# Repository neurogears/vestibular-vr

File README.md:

# vestibular-vr
Closed-loop VR setup for Rancz Lab

[Design Document](https://github.com/neurogears/vestibular-vr/blob/main/Design%20Documents/Vestibular%20VR%20Design%20Document.md)

### Acquisition Prerequisites

The following need to be installed on a fresh system in order to bootstrap the Bonsai environment correctly:

* Windows 10 or greater
* [Visual Studio Code](https://code.visualstudio.com/) (recommended for editing code scripts and git commits)
* [.NET 8.0 SDK](https://dotnet.microsoft.com/en-us/download/dotnet/8.0)
* [.NET Framework 4.7.2 Developer Pack](https://dotnet.microsoft.com/download/dotnet-framework/thank-you/net472-developer-pack-offline-installer) (required for intellisense when editing code scripts)
* [Git for Windows](https://gitforwindows.org/) (recommended for cloning and manipulating this repository)
* [Visual C++ Redistributable for Visual Studio 2012](https://www.microsoft.com/en-us/download/details.aspx?id=30679) (native dependency for OpenCV)
* [FTDI CDM Driver 2.12.28](https://www.ftdichip.com/Drivers/CDM/CDM21228_Setup.zip) (serial port drivers for HARP devices)
* [Spinnaker SDK 1.29.0.5](https://www.teledynevisionsolutions.com/support/support-center/software-firmware-downloads/iis/spinnaker-sdk-download/spinnaker-sdk--download-files) (device drivers for FLIR cameras, sign in required, look in the archived stable versions for 1.29.0.5)

### Setting up the Bonsai environment

To set up a Bonsai environment for running vestibular-vr, use the terminal to clone the repo into a local folder:

``` 
git clone https://github.com/neurogears/vestibular-vr.git
```

Now navigate into vestibular-vr/bonsai folder and run the `Setup.ps1` script (on Windows right-click > Run with powershell). Once all dependencies have been restored Bonsai can be launched in a local environment from the `.exe` in this folder.

### Session settings

Experiment parameters are based on a json schema (`schema.json` in the repo). Implementations of this schema are defined in `.yml` files provided by the user that are then loaded in the main Bonsai workflow to set up experiment parameters.

#### Working with schemas in Visual Studio Code
To create and edit schema implementations with full autcomplete and hinting, Visual Studio Code requires some extensions to be added:
* json (ZainChen.json)
* JSON Schema Validator (tberman.json-schema-validator)
* YAML (redhat.vscode-yaml)

#### Creating an experiment parameter file
To create an experiment parameter file based on the `schema`, create a new `.yml` file and add a reference to the `schema` at the top of the file

```
%YAML 1.1
---
# yaml-language-server: $schema=schema.json
```

The `schema` has two main groups of properties that define global experiment parameters, and block-specific parameters respectively, e.g.:

```
metadata:
  animalId: plimbo
  rootPath: D:/TrialLogicTestData/
  runGain: 0.0005

blocks: [
  &blockA
  {
    stimulus: {type: "grating"},
    totalRuntime: 20,
    runThreshold: 100,
    decayTimestep: 0.1,
    runThresholdDecay: -1,
    haltProbability: 0.5,
    haltProtocol: {
      minumumDelay: 0.1,
      randomDelay: 1.5,
      haltTime: 2,
      haltGain: 0
    }
  },
  &blockB
  {
    stimulus: {type: "cloud"},
    totalRuntime: 140,
    runThreshold: 200,
    decayTimestep: 0.1,
    runThresholdDecay: -1,
    haltProbability: 0.7,
    haltProtocol: {
      minumumDelay: 0.1,
      randomDelay: 0.5,
      haltTime: 0.5,
      haltGain: 0
    }
  },
  {<<: *blockA},
  {<<: *blockB}
]
```

The description of each parameter's effect on the Bonsai workflow, along with its type and default values are defined within `schema.json` itself. Note that where a parameter is not specifically set in the `.yml` the value will revert the default.

### Running an experiment
To run an experiment, run the Bonsai application from the local environment and open Main.bonsai. Use the property grid to select the desired experiment parameter `.yml` file.

### Gain settings
The `schema` has a number of gain settings that can be used to flexibly the define the relationship between real-time data sources (ball movement, encoder reading, file playback) and closed-loop outputs like visual field movement or motor movement. These gains are applied hierarchically with some affecting all calculations, and some defined per-block or per-source:

- `runGain` - global gain applied to all calculations
  - `blockGainModifier` - additional gain specific to a block
    - Visual: gains that contribute to visual field motion
      - `flowXToVisualGain` - gain applied to optical sensor X reading
      - `flowYToVisualGain` - gain applied to optical sensor Y reading
      - `rotaryToVisualGain` - gain applied to the rotary encoder reading
      - `playbackToVisualGain` - gain applied to the file playback data source
    - Motor: gains that contribute to motor motion
      - `flowXToMotorGain` - gain applied to optical sensor X reading
      - `flowYToMotorGain` - gain applied to optical sensor Y reading
      - `playbackToMotorGain` - gain applied to the file playback data source
  - `haltGain` - set as part of a `haltProtocol`. Applies a gain to all sources during a halt, block-specific.

We use the term 'procession' to describe the movement delta of the visual field or motor in response to an update from a data source (optical flow, playback etc.) on a given trial. Let `h` be a variable that describes whether a halt is currently happening (1 = halt happening, 0 = halt not happening), visual and motor processions are defined as:

```
visualProcession = (runGain * blockGainModifier) * (flowXToVisualGain*flowX + flowYToVisualGain*flowY + rotaryToVisualGain*encoder + playbackToVisualGain*playback) * (haltGain*h)
```
```
motorProcession = (runGain * blockGainModifier) * (flowXToMotorGain*flowX + flowYToMotorGain*flowY + playbackToVisualGain*playback) * (haltGain*h)
```

`motorProcession` is converted by the function `ToPulseInterval` to an immediate pulse interval command which is written to the motor. The conversion between this command and the speed of the motor is dependent on the hardware settings for pulse interval --> motor motion on the motor controller.
The relationship of `visualProcession` to visual field movement is dependent on the current visual stimulus being presented. For example for a gratings stimulus, the value represents the absolute phase angle of the gratings being shown. For a motion clouds stimulus, it represents the (wrapped) index of the motion cloud frame being shown.

Gains can be set to modify the contribution of a data source to procession, for example to specify a block where visual motion is only dependent on the X value of the flow sensor we can set:

```
# metadata
runGain: 0.0008 # represents final conversion from procession to visual angle
# block settings
blockGainModifier: 1 # block modifier does not scale input data sources
flowXToVisualGain: 1 # we want the X flow value to contribute
flowYToVisualGain: 0 # we don't want the Y flow value to contribute
rotaryToVisualGain: 0 # encoder reading should not contribute
playbackToVisualGain: 0 # playback source should not contribute
```

### Optical flow sensor smoothing

An average smoothing function is applied to the optical sensor reading. A `schema` parameter `flowSmoothing` is applied per-block which specifies a count of how many samples to smooth over, i.e. the length of the buffer to take an average, smoothed value from.

### Data logging
Data is logged according to the [Aeon.Acquisition](https://github.com/SainsburyWellcomeCentre/aeon_acquisition) format. Generally, data is grouped according to a folder named with a timestamp representing the start time of an experiment. Within this folder, data is organised by **device**, where a device may be a camera, Harp board, ONIX acquisition etc. For longer experiments, data is 'chunked' by hour such that the full raw data is split across multiple files to ensure no single file grows unmanageably large.

Within each device, data may be stored in a different format according to the device's data output. In general however, there will be a log of the raw data (e.g. camera frames, sensor readings) and a corresponding source of timestamps to allow for relating the data to the Harp clock. For a camera, this will take the form of a video file with the acquired camera frames, as well as a corresponding .csv file with paired Harp timestamps and camera frame indices. For a Harp device, this will take the form of a flat binary file organised by individual register, with the output of that register paired with a Harp timestamp.

As Harp files are saved as flat binary, it is recommended to use the device schema for that Harp device to parse the individual values and read the correct data type.

### Python environment

The following need to be installed once on a new system in order to analyze data:

 * [Visual Studio Code](https://code.visualstudio.com/) (recommended for editing code scripts and git commits)
 * A Conda distribution such as [Miniconda](https://docs.anaconda.com/free/miniconda/index.html)
 * [Python Extension for VS Code](https://marketplace.visualstudio.com/items?itemName=ms-python.python)
   * This extension needs to be made aware of the Conda installation. To do so, navigate to the extension settings. Under the section **Python: Conda Path**, enter the full path to the conda.bat executable. ([more info](https://stackoverflow.com/a/77615160/3312269).)
 * [Jupyter Extension for VS Code](https://marketplace.visualstudio.com/items?itemName=ms-toolsai.jupyter)

#### Create local Environment
1. Open the vestibular-vr folder in VS Code
2. `Ctrl+Shift+P` in VS Code > Python: Create Environment
   * Select Conda
   * Select Python 3.11 kernel
3. Ensure pip is upgraded:
 ```
 pip install --upgrade pip
 ```
4. From the terminal run `pip install -r requirements.txt`
5. Clone aeon_mecha into a separate directory 
 ```
 git clone https://github.com/SainsburyWellcomeCentre/aeon_mecha.git 
 ```
6. From the VS Code terminal, `cd` into the aeon_mecha directory and run:
 ```
 python -m pip install -e .
 ```

 ### SLEAP
 Follow the standard instructions for [installing SLEAP](https://sleap.ai/installation.html), [creating a project](https://sleap.ai/tutorials/new-project.html) and [labeling](https://sleap.ai/tutorials/initial-labeling.html). Ensure that you use training videos of the same pixel width and height that you will use for inference later. During training, ensure you select `single animal` as the training pipeline type, and that the image is converted to grayscale.

 After completing training, activate the sleap conda environment (if not already activated) and run:

 ```
sleap-export -m /model/folder/path
 ```

 to export the trained model to a format that can be used by Bonsai.

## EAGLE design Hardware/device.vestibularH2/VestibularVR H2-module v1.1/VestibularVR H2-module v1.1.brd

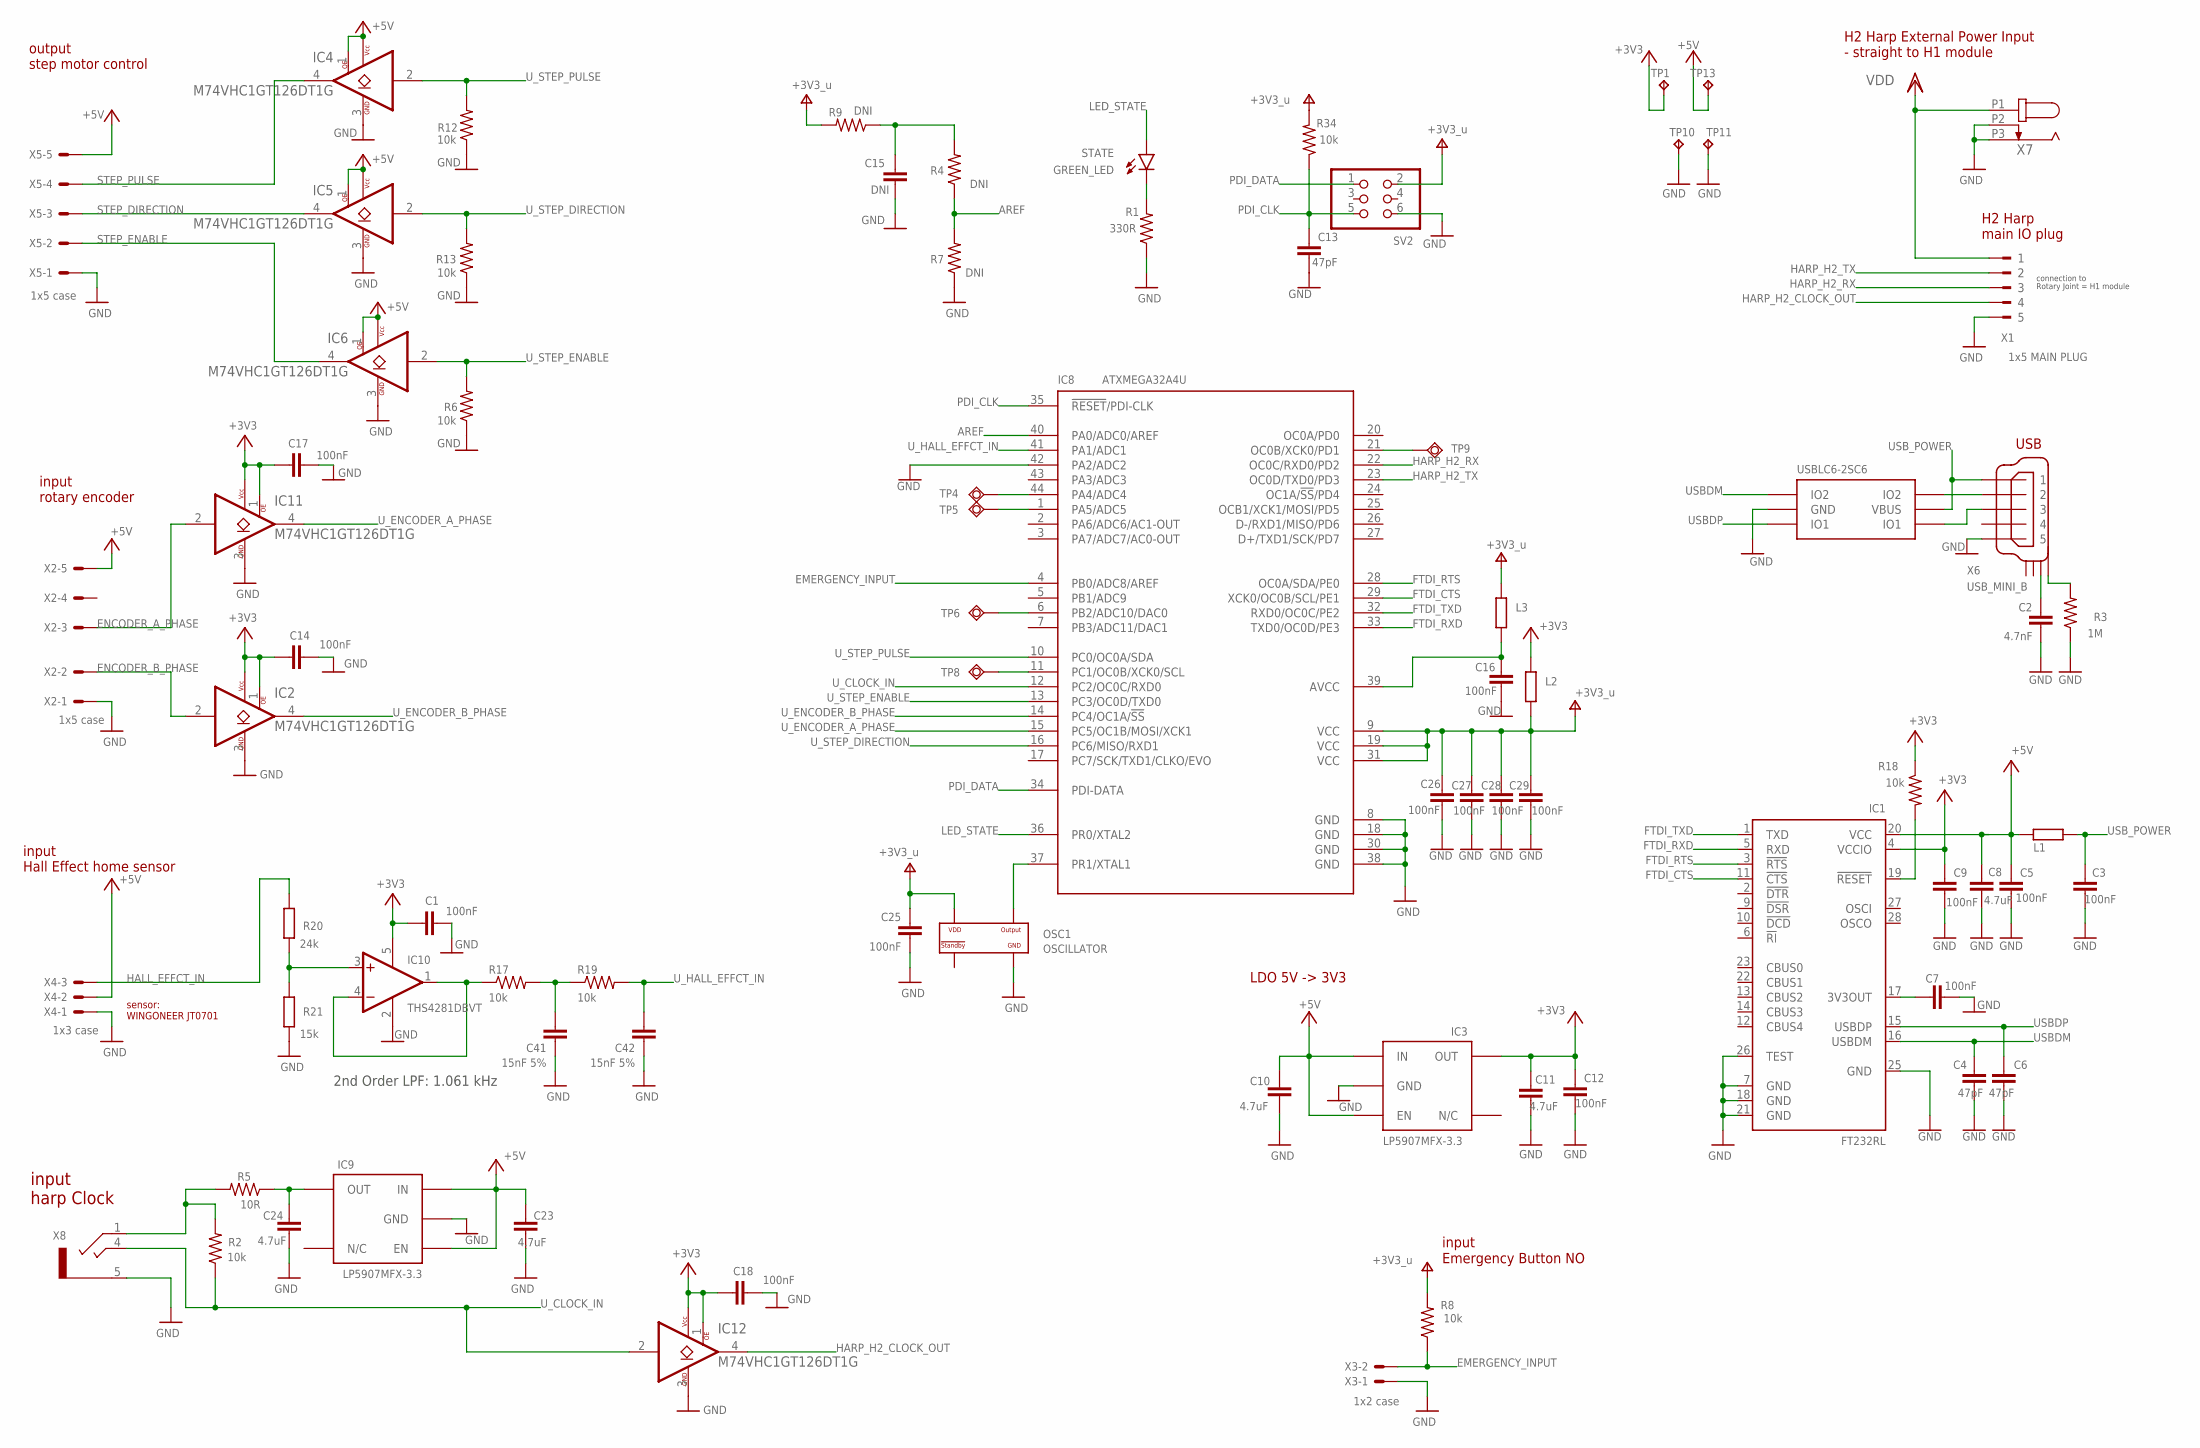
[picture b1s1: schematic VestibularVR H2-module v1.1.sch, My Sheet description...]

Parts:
C1, C3, C5, C7, C9, C12, C14, C16, C17, C18, C25, C26, C27, C28, C29: 100nF; C0402K; MPN C1005X7R1H104K050BB
C2: 4.7nF; C0402K; MPN CC0402KRX7R8BB472
C4, C6, C13: 47pF; C0402K; MPN 04025A470JAT2A
C8, C10, C11, C23, C24: 4.7uF; C0603K; MPN C1608X6S1C475K080AC
C15: DNI; C0603K; MPN DNI
C41, C42: 15nF 5%; C0402K; MPN CGA2B3X7R1V153K050BB
IC1: FT232RL; SSOP28; MPN FT232RL
IC2, IC4, IC5, IC6, IC11, IC12: M74VHC1GT126DT1G; TSOP-5; MPN M74VHC1GT126DT1G; DIGIKEY_PN M74VHC1GT126DT1GOSDKR-ND
IC3, IC9: LP5907MFX-3.3; TSOT23-5; MPN LP5907MFX-3.3/NOPB
IC7: USBLC6-2SC6; SOT23-6L; MPN USBLC6-2SC6
IC8: ATXMEGA32A4U; TQFP44; MPN ATXMEGA32A4U-AUR
IC10: THS4281DBVT; SOT23-5; MPN THS4281DBVT
L1, L2, L3: 40R@100MHz; R0805; MPN MI0805K400R-10
OSC1: OSCILLATOR; OSCILLATOR_3.2X2.5; MPN DSC1001CI5-032.0000
R1: 330R; R0402; MPN RC0402FR-07330RL
R2, R6, R8, R12, R13, R17, R18, R19, R34: 10k; R0402; MPN CRCW040210K0FKED
R3: 1M; R0402; MPN CRCW04021M00FKED
R4, R7, R9: DNI; R0402; MPN DNI
R5: 10R; R0402; MPN ERJ-PA2J100X
R20: 24k; R0402; MPN ERJ-2RKF2402X
R21: 15k; R0402; MPN ERJ-2RKF1502X
STATE: GREEN_LED; CHIP-LED0603; MPN LTST-C191KGKT
SV2: PINHD-2X3; 2X03; MPN 609-3210-ND
TP1, TP10, TP11, TP13: NO_COMPONENT; B1,27
TP4, TP5, TP6, TP8, TP9: NO_COMPONENT; TP11R
X1: 1x5 MAIN PLUG; 90G-5; MPN 20.155MH/5-E
X2, X5: 1x5 case; 22-23-2051; MPN 282834-5
X3: 1x2 case; 22-23-2021; MPN 282834-2
X4: 1x3 case; 22-23-2031; MPN 282834-3
X6: USB_MINI_B; 240-0002-1; MPN UX60-MB-5S8
X7: DC_JACK2.1MM; DC_POWER_INPUT_2.1MM; MPN 163-179PH-EX
X8: CLCK_JACK; 35RASMT2BHNTRX; MPN 35RASMT2BHNTRX

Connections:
+3V3: C1.1, C9.1, C11.1, C12.1, C14.1, C17.1, C18.1, IC1.4 (VCCIO), IC2.1 (OE), IC2.5 (VCC), IC3.5 (OUT), IC10.5 (V+), IC11.1 (OE), IC11.5 (VCC), IC12.1 (OE), IC12.5 (VCC), L2.2, R18.1, TP1.TP
+5V: C5.1, C8.1, C10.1, C23.1, IC1.20 (VCC), IC3.1 (IN), IC3.3 (EN), IC4.1 (OE), IC4.5 (VCC), IC5.1 (OE), IC5.5 (VCC), IC6.1 (OE), IC6.5 (VCC), IC9.1 (IN), IC9.3 (EN), L1.1, TP13.TP, X2.5, X4.2, X5.5
AREF: IC8.40 (PA0/ADC0/AREF), R4.1, R7.2
EMERGENCY_INPUT: IC8.4 (PB0/ADC8/AREF), R8.1, X3.2
ENCODER_A_PHASE: IC11.2 (A), X2.3
ENCODER_B_PHASE: IC2.2 (A), X2.2
FTDI_CTS: IC1.11 (!CTS), IC8.29 (XCK0/OC0B/SCL/PE1)
FTDI_RTS: IC1.3 (!RTS), IC8.28 (OC0A/SDA/PE0)
FTDI_RXD: IC1.5 (RXD), IC8.33 (TXD0/OC0D/PE3)
FTDI_TXD: IC1.1 (TXD), IC8.32 (RXD0/OC0C/PE2)
GND: C1.2, C2.2, C3.2, C4.2, C5.2, C6.2, C7.2, C8.2, C9.2, C10.2, C11.2, C12.2, C13.2, C14.2, C15.2, C16.2, C17.2, C18.2, C23.2, C24.2, C25.2, C26.2, C27.2, C28.2, C29.2, C41.1, C42.1, IC1.7 (GND), IC1.18 (GND), IC1.21 (GND), IC1.25 (GND), IC1.26 (TEST), IC2.3 (GND), IC3.2 (GND), IC4.3 (GND), IC5.3 (GND), IC6.3 (GND), IC7.P$2 (GND), IC8.8 (GND), IC8.18 (GND), IC8.30 (GND), IC8.38 (GND), IC8.42 (PA2/ADC2), IC9.2 (GND), IC10.2 (V-), IC11.3 (GND), IC12.3 (GND), OSC1.P$2 (GND), R1.1, R3.1, R6.1, R7.1, R12.1, R13.1, R21.1, SV2.6, TP10.TP, TP11.TP, X1.5, X2.1, X3.1, X4.1, X5.1, X6.P$5 (5), X7.P2 (2), X7.P3 (3), X8.5
HALL_EFFCT_IN: R20.2, X4.3
HARP_H2_CLOCK_OUT: IC12.4 (Y), X1.4
HARP_H2_RX: IC8.22 (OC0C/RXD0/PD2), X1.3
HARP_H2_TX: IC8.23 (OC0D/TXD0/PD3), X1.2
LED_STATE: IC8.36 (PR0/XTAL2), STATE.A
unnamed: R3.2, X6.SHIELD_4
unnamed: IC7.P$4 (IO2), X6.P$2 (2)
unnamed: IC7.P$6 (IO1), X6.P$3 (3)
unnamed: R1.2, STATE.C
unnamed: IC8.44 (PA4/ADC4), TP4.TP
unnamed: IC8.1 (PA5/ADC5), TP5.TP
unnamed: IC8.6 (PB2/ADC10/DAC0), TP6.TP
unnamed: C2.1, X6.SHIELD_3
unnamed: IC8.11 (PC1/OC0B/XCK0/SCL), TP8.TP
unnamed: IC8.21 (OC0B/XCK0/PD1), TP9.TP
unnamed: C7.1, IC1.17 (3V3OUT)
unnamed: C41.2, R17.2, R19.1
unnamed: C15.1, R4.2, R9.1
unnamed: C16.1, IC8.39 (AVCC), L3.1
unnamed: IC10.1 (OUT), IC10.4 (-IN), R17.1
unnamed: IC10.3 (+IN), R20.1, R21.2
unnamed: R2.2, R5.2, X8.1
unnamed: C24.1, IC9.5 (OUT), R5.1
unnamed: IC1.19 (!RESET), R18.2
OSC2: IC8.37 (PR1/XTAL1), OSC1.P$3 (OUTPUT)
PDI_CLK: C13.1, IC8.35 (!RESET!/PDI-CLK), R34.1, SV2.5
PDI_DATA: IC8.34 (PDI-DATA), SV2.1
STEP_DIRECTION: IC5.4 (Y), X5.3
STEP_ENABLE: IC6.4 (Y), X5.2
STEP_PULSE: IC4.4 (Y), X5.4
USBDM: C4.1, IC1.16 (USBDM), IC7.P$3 (IO2)
USBDP: C6.1, IC1.15 (USBDP), IC7.P$1 (IO1)
USB_POWER: C3.1, IC7.P$5 (VBUS), L1.2, X6.P$1 (1)
U_CLOCK_IN: IC8.12 (PC2/OC0C/RXD0), IC12.2 (A), R2.1, X8.4
U_ENCODER_A_PHASE: IC8.15 (PC5/OC1B/MOSI/XCK1), IC11.4 (Y)
U_ENCODER_B_PHASE: IC2.4 (Y), IC8.14 (PC4/OC1A/!SS)
U_HALL_EFFCT_IN: C42.2, IC8.41 (PA1/ADC1), R19.2
U_STEP_DIRECTION: IC5.2 (A), IC8.16 (PC6/MISO/RXD1), R13.2
U_STEP_ENABLE: IC6.2 (A), IC8.13 (PC3/OC0D/TXD0), R6.2
U_STEP_PULSE: IC4.2 (A), IC8.10 (PC0/OC0A/SDA), R12.2
V+: C25.1, C26.1, C27.1, C28.1, C29.1, IC8.9 (VCC), IC8.19 (VCC), IC8.31 (VCC), L2.1, L3.2, OSC1.P$4 (VDD), R8.2, R9.2, R34.2, SV2.2
VDD: X1.1, X7.P1 (1)

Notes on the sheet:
H2 Harp main IO plug
input rotary encoder
input Hall Effect home sensor
input harp Clock
output step motor control
input Emergency Button NO
USB
sensor: WINGONEER JT0701
H2 Harp External Power Input - straight to H1 module
connection to Rotary Joint = H1 module
2nd Order LPF: 1.061 kHz
LDO 5V -> 3V3

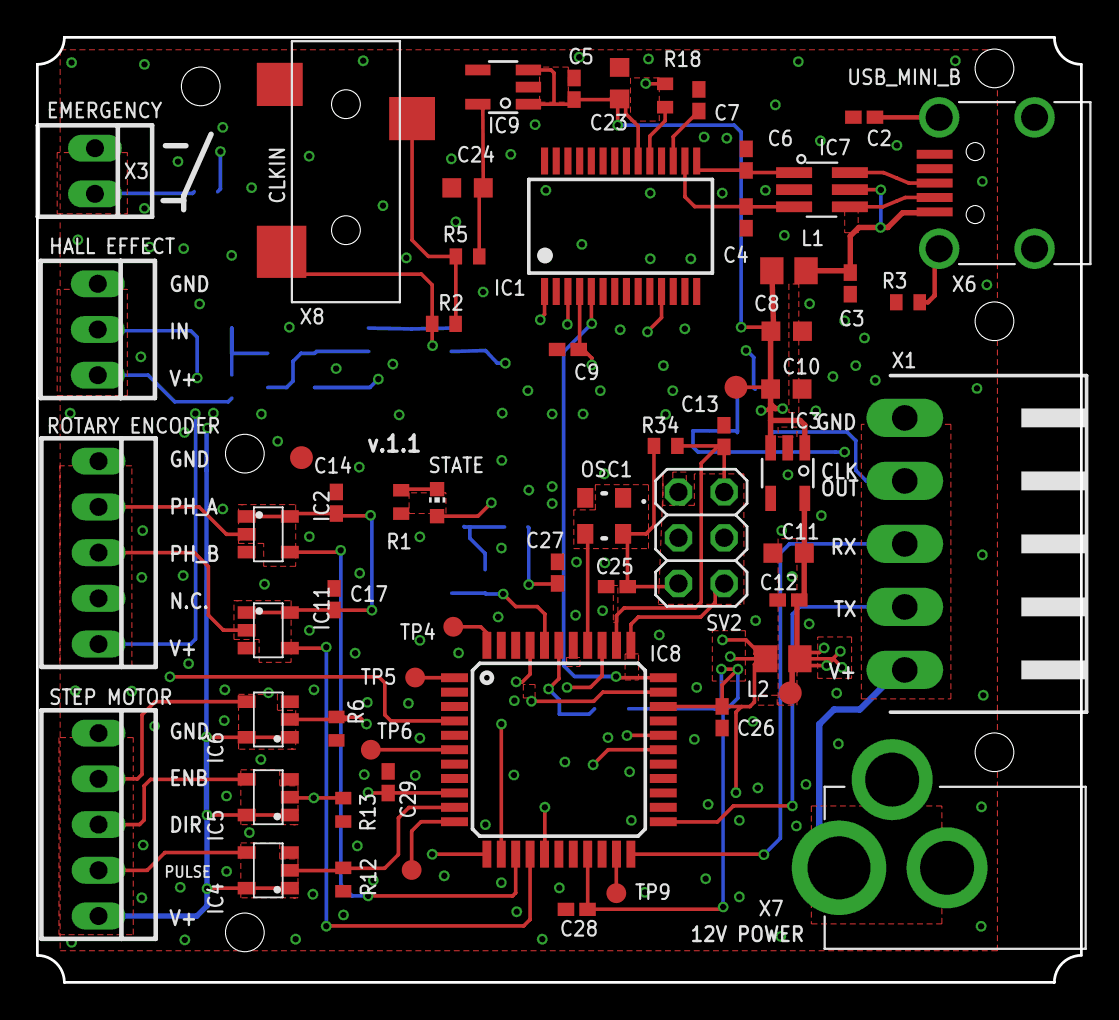
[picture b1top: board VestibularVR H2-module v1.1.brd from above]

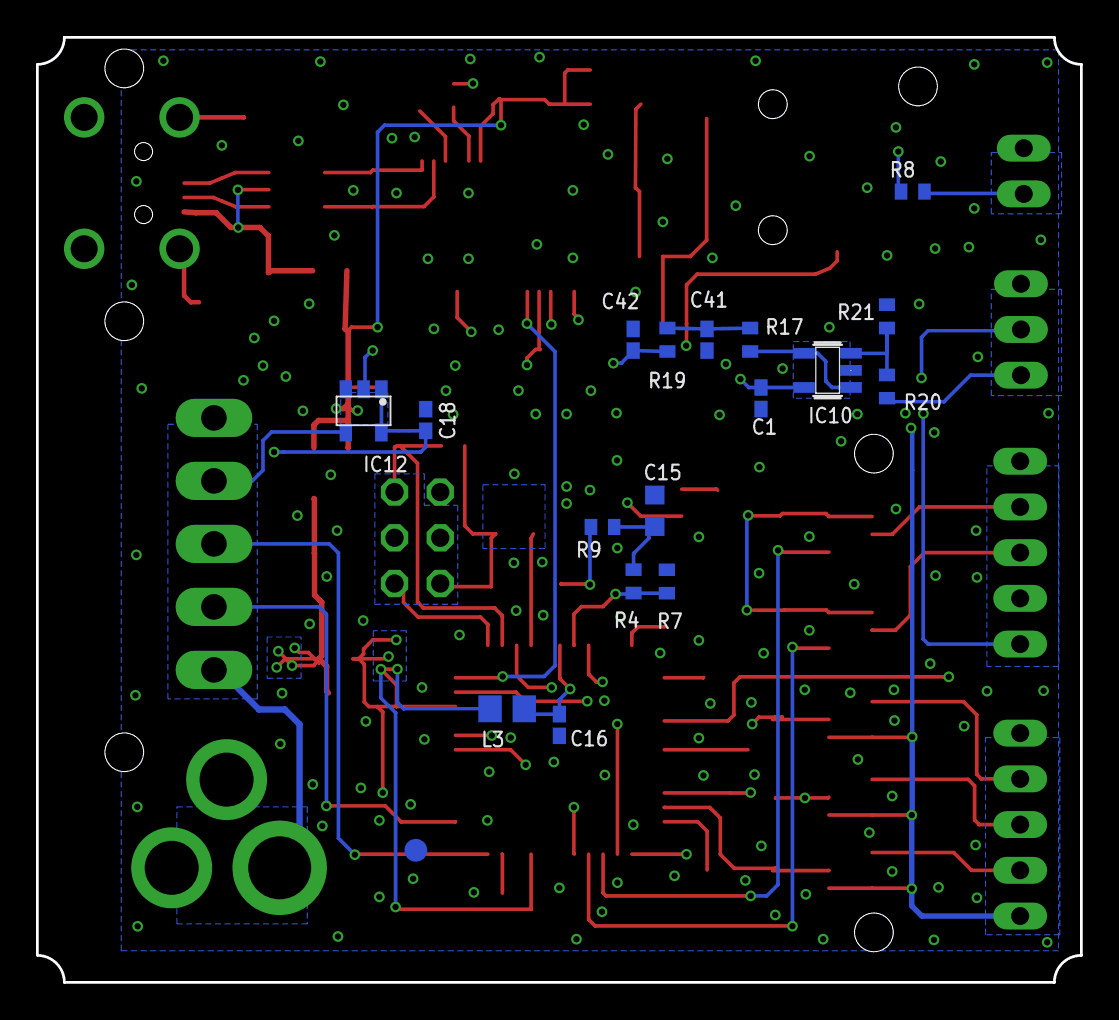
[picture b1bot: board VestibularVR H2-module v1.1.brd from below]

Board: 4 copper layers, 58.0 x 52.5 mm, 79 parts (18 on the bottom side), 53 nets.

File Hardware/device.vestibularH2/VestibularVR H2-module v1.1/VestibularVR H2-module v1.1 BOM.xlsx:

VestibularVR H2-module v1.1
.on board
Qty | Parts | Value | OEPS | MPN | Device | Package | Description
15 | C1, C3, C5, C7, C9, C12, C14, C16, C17, C18, C25, C26, C27, C28, C29 | 100nF | OEPS010004 | C1005X7R1H104K050BB | C-EUC0402K | C0402K | CAPACITOR, European symbol
1 | R5 | 10R | OEPS020041 | ERJ-PA2J100X | R-US_R0402 | R0402 | RESISTOR, American symbol
9 | R2, R6, R8, R12, R13, R17, R18, R19, R34 | 10k | OEPS020030 | CRCW040210K0FKED | R-US_R0402 | R0402 | RESISTOR, American symbol
1 | R21 | 15k | OEPS020015 | ERJ-2RKF1502X | R-EU_R0402 | R0402 | RESISTOR, European symbol
2 | C41, C42 | 15nF 5% | OEPS010023 | CGA2B3X7R1V153K050BB | C-EUC0402K | C0402K | CAPACITOR, European symbol
1 | R3 | 1M | OEPS020026 | CRCW04021M00FKED | R-US_R0402 | R0402 | RESISTOR, American symbol
1 | X3 | 1x2 case | OEPS070020 | 282834-2 | 22-23-2021 | 22-23-2021 | .100 (2.54mm) Center Header - 2 Pin"
1 | X4 | 1x3 case | OEPS070035 | 282834-3 | 22-23-2031 | 22-23-2031 | .100 (2.54mm) Center Header - 3 Pin"
1 | X1 | 1x5 MAIN PLUG | OEPS070037 | 20.155MH/5-E | 90G-5 | 90G-5 | WEIDMUELLER CLAMP CONNECTOR
2 | X2, X5 | 1x5 case | OEPS070041 | 282834-5 | 22-23-2051 | 22-23-2051 | .100 (2.54mm) Center Header - 5 Pin"
1 | R20 | 24k | OEPS020048 | ERJ-2RKF2402X | R-EU_R0402 | R0402 | RESISTOR, European symbol
1 | R1 | 330R | OEPS020037 | RC0402FR-07330RL | R-US_R0402 | R0402 | RESISTOR, American symbol
1 | C2 | 4.7nF | OEPS010001 | CC0402KRX7R8BB472 | C-EUC0402K | C0402K | CAPACITOR, European symbol
5 | C8, C10, C11, C23, C24 | 4.7uF | OEPS010018 | C1608X6S1C475K080AC | C-EUC0603K | C0603K | CAPACITOR, European symbol
3 | L1, L2, L3 | 40R@100MHz | OEPS040003 | MI0805K400R-10 | R-EU_R0805 | R0805 | RESISTOR, European symbol
3 | C4, C6, C13 | 47pF | OEPS010011 | 04025A470JAT2A | C-EUC0402K | C0402K | CAPACITOR, European symbol
1 | IC8 | ATXMEGA32A4U | OEPS080012 | ATXMEGA32A4U-AUR | XMEGA-A4_AT-XMEGA-XXA4-AUTQFP44 | TQFP44 | ATxMega a4 Serie
1 | X8 | CLCK_JACK | OEPS070025 | 35RASMT2BHNTRX | STEREO_JACK | 35RASMT2BHNTRX | CONN JACK STEREO 3.5MM SMD R/A
1 | X7 | DC_JACK2.1MM | OEPS070026 | 163-179PH-EX | DC_JACK2.1MM | DC_POWER_INPUT_2.1MM | DC Power Connectors PCB 2.1MM
1 | C15 | DNI | DNI | DNI | C-EUC0603K | C0603K | CAPACITOR, European symbol
3 | R4, R7, R9 | DNI | DNI | DNI | R-US_R0402 | R0402 | RESISTOR, American symbol
1 | IC1 | FT232RL | OEPS080013 | FT232RL | FT232RL | SSOP28 | UART/FIFO IC
1 | STATE | GREEN_LED | OEPS030005 | LTST-C191KGKT | LEDCHIP-LED0603 | CHIP-LED0603
2 | IC3, IC9 | LP5907MFX-3.3 | OEPS080016 | LP5907MFX-3.3/NOPB | TLV700XX | TSOT23-5 | C REG LINEAR 3.3V 200MA SOT23-5
6 | IC2, IC4, IC5, IC6, IC11, IC12 | M74VHC1GT126DT1G | OEPS080017 | M74VHC1GT126DT1G | M74VHC1GT126DT1G | TSOP-5
1 | OSC1 | OSCILLATOR | OEPS080018 | DSC1001CI5-032.0000 | OSCILLATOR | OSCILLATOR_3.2X2.5 | XTAL OSC TCXO 32.0000MHZ HCMOS
1 | SV2 | PINHD-2X3 | OEPS070015 | 609-3210-ND | PINHD-2X3 | 2X03 | PIN HEADER
1 | IC10 | THS4281DBVT | OEPS080038 | THS4281DBVT | OPA365 | SOT23-5
1 | IC7 | USBLC6-2SC6 | OEPS030010 | USBLC6-2SC6 | USBLC6-2SC6 | SOT23-6L | TVS DIODE 5.25VWM 17VC SOT23-6
1 | X6 | USB_MINI_B | OEPS070021 | UX60-MB-5S8 | USB_MINI_B | 240-0002-1 | CONN RCPT USB2.0 MINI B SMD R/A
.off board
N.A.

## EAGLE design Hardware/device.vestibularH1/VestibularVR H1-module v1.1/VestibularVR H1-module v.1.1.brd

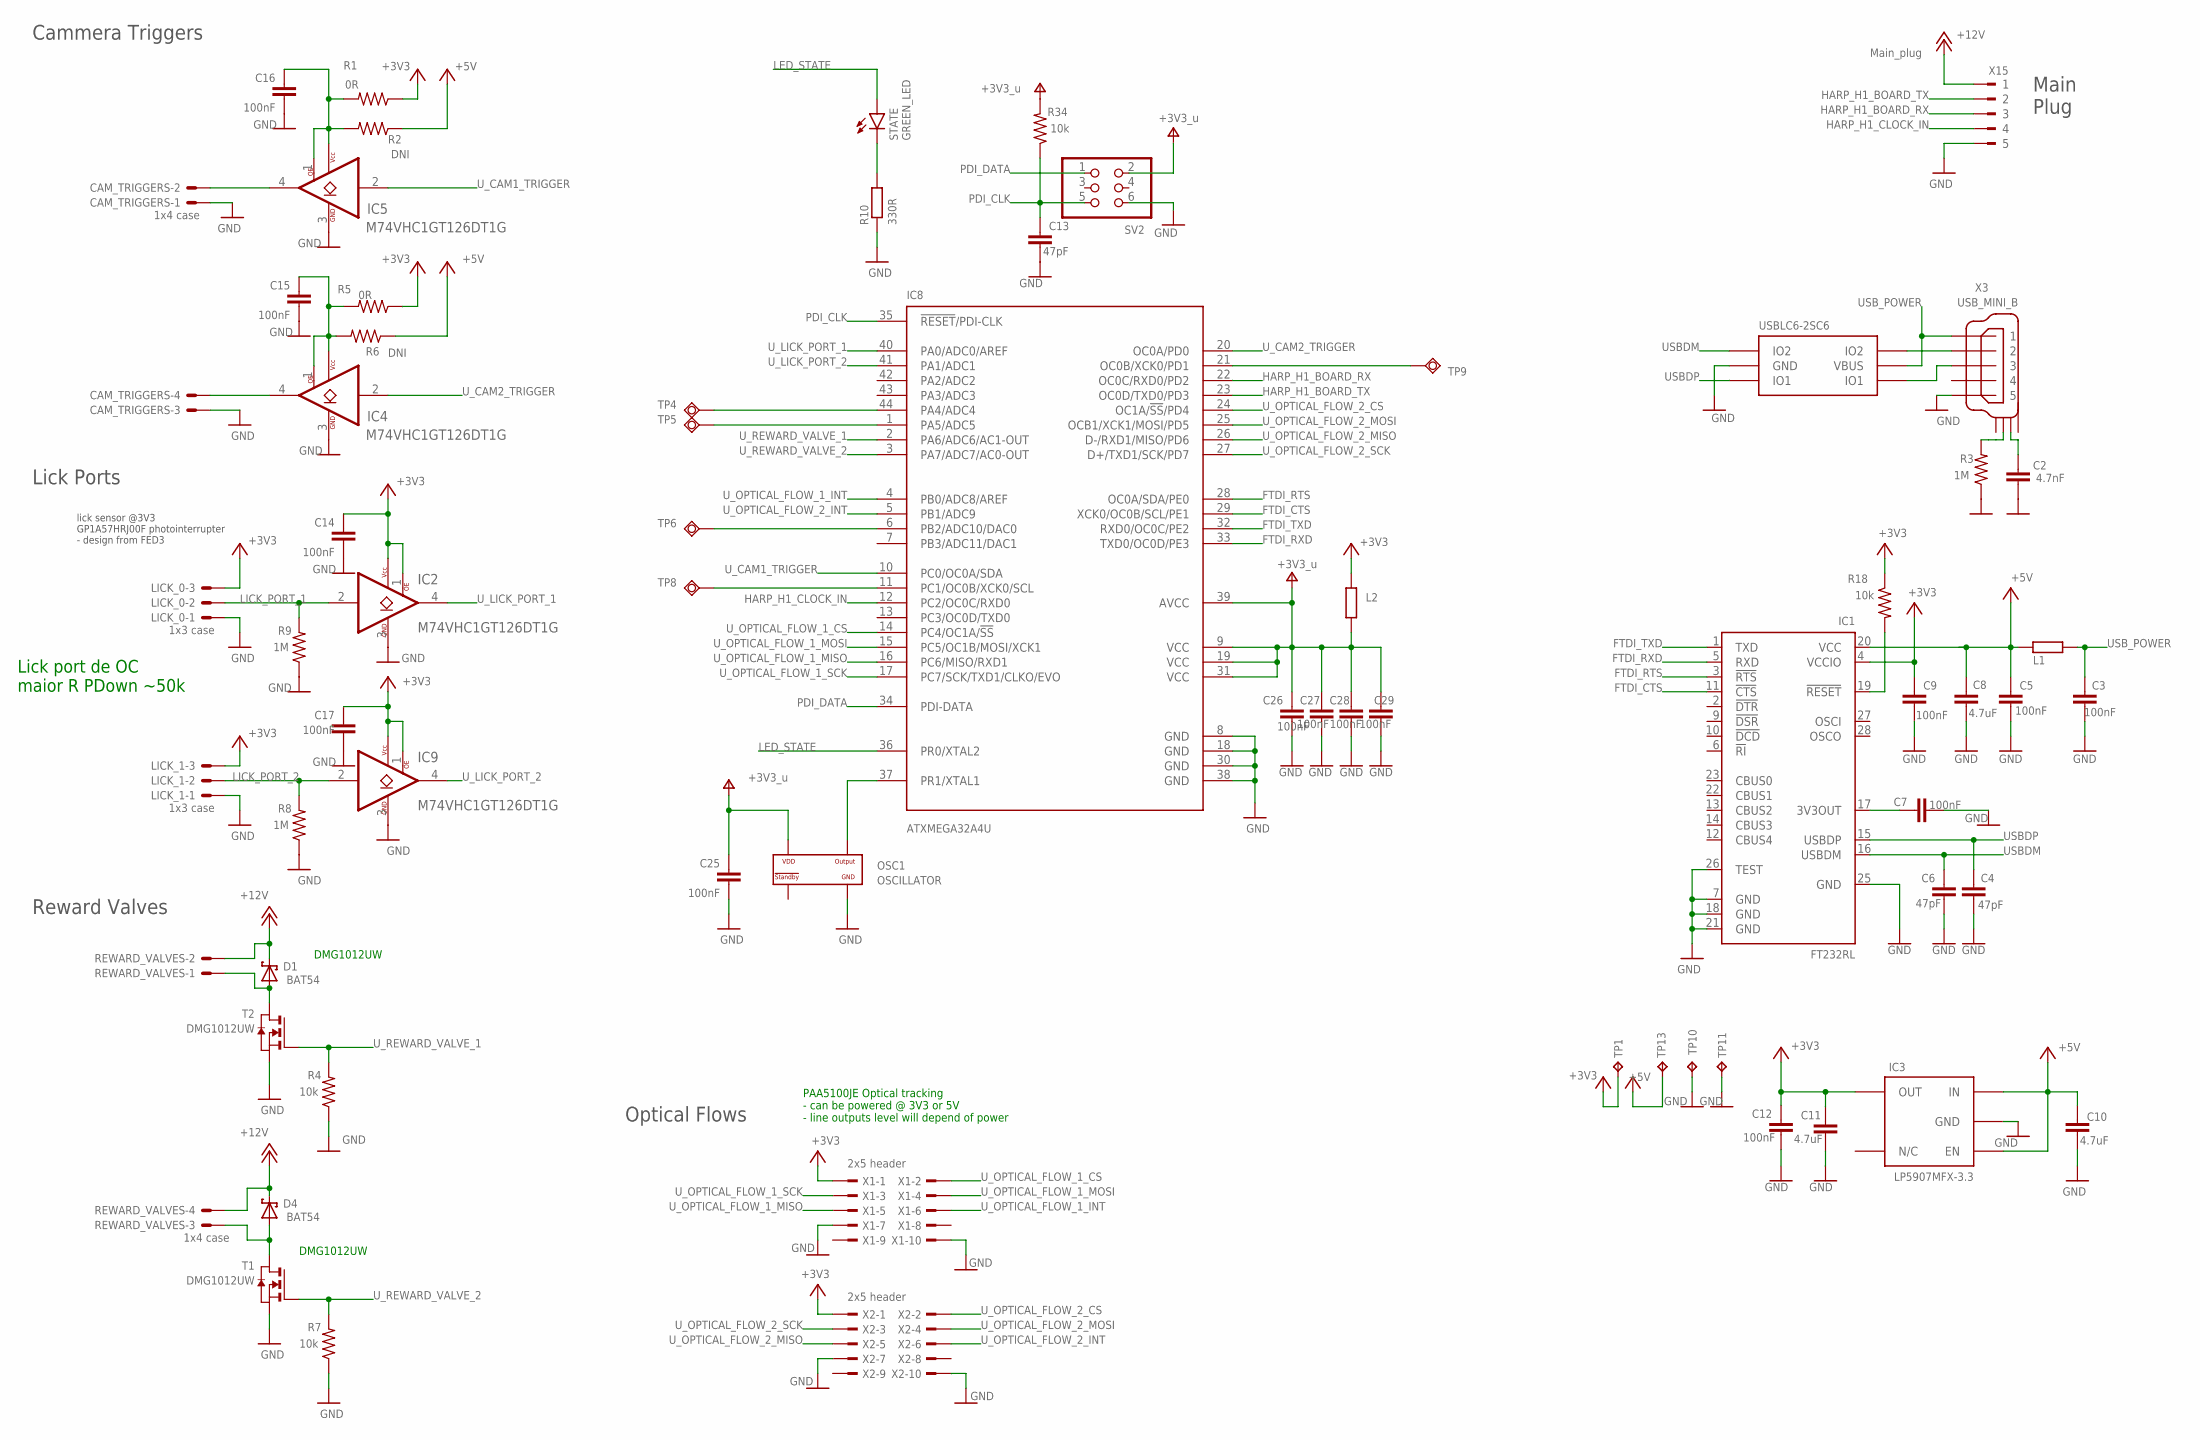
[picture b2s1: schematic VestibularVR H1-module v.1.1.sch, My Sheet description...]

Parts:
C2: 4.7nF; C0402K; MPN CC0402KRX7R8BB472
C3, C5, C7, C9, C12, C14, C15, C16, C17, C25, C26, C27, C28, C29: 100nF; C0402K; MPN C1005X7R1H104K050BB; DIGIKEY_PN 445-5932-1-ND
C4, C6, C13: 47pF; C0402K; MPN 04025A470JAT2A
C8: 4.7uF; C0603; MPN C1608X6S1C475K080AC
C10, C11: 4.7uF; C0603K; MPN C1608X6S1C475K080AC
CAM_TRIGGERS: 1x4 case; 22-23-2041; MPN 282834-4
D1, D4: BAT54; SOT23; MPN BAT54SLT1G
IC1: FT232RL; SSOP28; MPN FT232RL
IC2, IC4, IC5, IC9: M74VHC1GT126DT1G; TSOP-5; MPN M74VHC1GT126DT1G; DIGIKEY_PN M74VHC1GT126DT1GOSDKR-ND
IC3: LP5907MFX-3.3; TSOT23-5; MPN LP5907MFX-3.3/NOPB
IC7: USBLC6-2SC6; SOT23-6L; MPN USBLC6-2SC6
IC8: ATXMEGA32A4U; TQFP44
L1, L2: 40R@100MHz; R0603; MPN MI0805K400R-10
LICK_0, LICK_1: 1x3 case; 22-23-2031; MPN 282834-3
OSC1: OSCILLATOR; OSCILLATOR_3.2X2.5; MPN DSC1001CI5-032.0000
R1, R5: 0R; R0402@1; MPN RC0402JR-070RL
R2, R6: DNI; R0402@1; MPN DNI
R3, R8, R9: 1M; R0402@1; MPN CRCW04021M00FKED; DIGIKEY_PN 541-1.00MLCT-ND
R4, R7, R18, R34: 10k; R0402@1; MPN CRCW040210K0FKED; DIGIKEY_PN 541-10.0KLDKR-ND
R10: 330R; R0402; MPN RC0402FR-07330RL
REWARD_VALVES: 1x4 case; 22-23-2041; MPN 282834-4
STATE: GREEN_LED; CHIP-LED0603; MPN LTST-C191KGKT
SV2: PINHD-2X3; 2X03; MPN 609-3210-ND
T1, T2: DMG1012UW; SOT323; MPN DMG1012UW-7
TP1, TP10, TP11, TP13: NO_COMPONENT; B1,27
TP4, TP5, TP6, TP8, TP9: NO_COMPONENT; TP11R
X1, X2: 2x5 header; TSW-105-02-S-D; MPN 2x5 header
X3: USB_MINI_B; 240-0002-1; MPN UX60-MB-5S8
X15: Main_plug; 90G-5; MPN 20.155MH/5-E

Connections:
+3V3: C9.1, C11.1, C12.1, C14.1, C17.1, IC1.4 (VCCIO), IC2.1 (OE), IC2.5 (VCC), IC3.5 (OUT), IC9.1 (OE), IC9.5 (VCC), L2.2, LICK_0.3, LICK_1.3, R1.1, R5.1, R18.1, TP1.TP, X1.1, X2.1
+3V3_U: C25.1, C26.1, C27.1, C28.1, C29.1, IC8.9 (VCC), IC8.19 (VCC), IC8.31 (VCC), IC8.39 (AVCC), L2.1, OSC1.P$4 (VDD), R34.2, SV2.2
+5V: C5.1, C8.1, C10.1, IC1.20 (VCC), IC3.1 (IN), IC3.3 (EN), L1.1, R2.1, R6.1, TP13.TP
+12V: D1.3 (C), D4.3 (C), REWARD_VALVES.2, REWARD_VALVES.4, X15.1
FTDI_CTS: IC1.11 (!CTS), IC8.29 (XCK0/OC0B/SCL/PE1)
FTDI_RTS: IC1.3 (!RTS), IC8.28 (OC0A/SDA/PE0)
FTDI_RXD: IC1.5 (RXD), IC8.33 (TXD0/OC0D/PE3)
FTDI_TXD: IC1.1 (TXD), IC8.32 (RXD0/OC0C/PE2)
GND: C2.2, C3.2, C4.2, C5.2, C6.2, C7.2, C8.2, C9.2, C10.2, C11.2, C12.2, C13.2, C14.2, C15.2, C16.2, C17.2, C25.2, C26.2, C27.2, C28.2, C29.2, CAM_TRIGGERS.1, CAM_TRIGGERS.3, IC1.7 (GND), IC1.18 (GND), IC1.21 (GND), IC1.25 (GND), IC1.26 (TEST), IC2.3 (GND), IC3.2 (GND), IC4.3 (GND), IC5.3 (GND), IC7.P$2 (GND), IC8.8 (GND), IC8.18 (GND), IC8.30 (GND), IC8.38 (GND), IC9.3 (GND), LICK_0.1, LICK_1.1, OSC1.P$2 (GND), R3.1, R4.1, R7.1, R8.1, R9.1, R10.1, SV2.6, T1.2 (S), T2.2 (S), TP10.TP, TP11.TP, X1.7, X1.10, X2.7, X2.10, X3.P$5 (5), X15.5
HARP_H1_BOARD_RX: IC8.22 (OC0C/RXD0/PD2), X15.3
HARP_H1_BOARD_TX: IC8.23 (OC0D/TXD0/PD3), X15.2
HARP_H1_CLOCK_IN: IC8.12 (PC2/OC0C/RXD0), X15.4
LED_STATE: IC8.36 (PR0/XTAL2), STATE.A
LICK_PORT_1: IC2.2 (A), LICK_0.2, R9.2
LICK_PORT_2: IC9.2 (A), LICK_1.2, R8.2
unnamed: R3.2, X3.SHIELD_2
unnamed: IC7.P$4 (IO2), X3.P$2 (2)
unnamed: IC7.P$6 (IO1), X3.P$3 (3)
unnamed: CAM_TRIGGERS.4, IC4.4 (Y)
unnamed: C16.1, IC5.1 (OE), IC5.5 (VCC), R1.2, R2.2
unnamed: D4.1 (A), REWARD_VALVES.3, T1.3 (D)
unnamed: CAM_TRIGGERS.2, IC5.4 (Y)
unnamed: R10.2, STATE.C
unnamed: IC8.44 (PA4/ADC4), TP4.TP
unnamed: IC8.1 (PA5/ADC5), TP5.TP
unnamed: IC8.6 (PB2/ADC10/DAC0), TP6.TP
unnamed: C15.1, IC4.1 (OE), IC4.5 (VCC), R5.2, R6.2
unnamed: C2.1, X3.SHIELD_3
unnamed: IC8.11 (PC1/OC0B/XCK0/SCL), TP8.TP
unnamed: IC8.21 (OC0B/XCK0/PD1), TP9.TP
unnamed: C7.1, IC1.17 (3V3OUT)
unnamed: D1.1 (A), REWARD_VALVES.1, T2.3 (D)
unnamed: IC1.19 (!RESET), R18.2
OSC2: IC8.37 (PR1/XTAL1), OSC1.P$3 (OUTPUT)
PDI_CLK: C13.1, IC8.35 (!RESET!/PDI-CLK), R34.1, SV2.5
PDI_DATA: IC8.34 (PDI-DATA), SV2.1
USBDM: C6.1, IC1.16 (USBDM), IC7.P$3 (IO2)
USBDP: C4.1, IC1.15 (USBDP), IC7.P$1 (IO1)
USB_POWER: C3.1, IC7.P$5 (VBUS), L1.2, X3.P$1 (1)
U_CAM1_TRIGGER: IC5.2 (A), IC8.10 (PC0/OC0A/SDA)
U_CAM2_TRIGGER: IC4.2 (A), IC8.20 (OC0A/PD0)
U_LICK_PORT_1: IC2.4 (Y), IC8.40 (PA0/ADC0/AREF)
U_LICK_PORT_2: IC8.41 (PA1/ADC1), IC9.4 (Y)
U_OPTICAL_FLOW_1_CS: IC8.14 (PC4/OC1A/!SS), X1.2
U_OPTICAL_FLOW_1_INT: IC8.4 (PB0/ADC8/AREF), X1.6
U_OPTICAL_FLOW_1_MISO: IC8.16 (PC6/MISO/RXD1), X1.5
U_OPTICAL_FLOW_1_MOSI: IC8.15 (PC5/OC1B/MOSI/XCK1), X1.4
U_OPTICAL_FLOW_1_SCK: IC8.17 (PC7/SCK/TXD1/CLKO/EVO), X1.3
U_OPTICAL_FLOW_2_CS: IC8.24 (OC1A/!SS!/PD4), X2.2
U_OPTICAL_FLOW_2_INT: IC8.5 (PB1/ADC9), X2.6
U_OPTICAL_FLOW_2_MISO: IC8.26 (D-/RXD1/MISO/PD6), X2.5
U_OPTICAL_FLOW_2_MOSI: IC8.25 (OCB1/XCK1/MOSI/PD5), X2.4
U_OPTICAL_FLOW_2_SCK: IC8.27 (D+/TXD1/SCK/PD7), X2.3
U_REWARD_VALVE_1: IC8.2 (PA6/ADC6/AC1-OUT), R4.2, T2.1 (G)
U_REWARD_VALVE_2: IC8.3 (PA7/ADC7/AC0-OUT), R7.2, T1.1 (G)

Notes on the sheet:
lick sensor @3V3 GP1A57HRJ00F photointerrupter - design from FED3
PAA5100JE Optical tracking - can be powered @ 3V3 or 5V - line outputs level will depend of power
Reward Valves
Lick Ports
Cammera Triggers
Main Plug
Optical Flows
Lick port de OC maior R PDown ~50k
DMG1012UW
